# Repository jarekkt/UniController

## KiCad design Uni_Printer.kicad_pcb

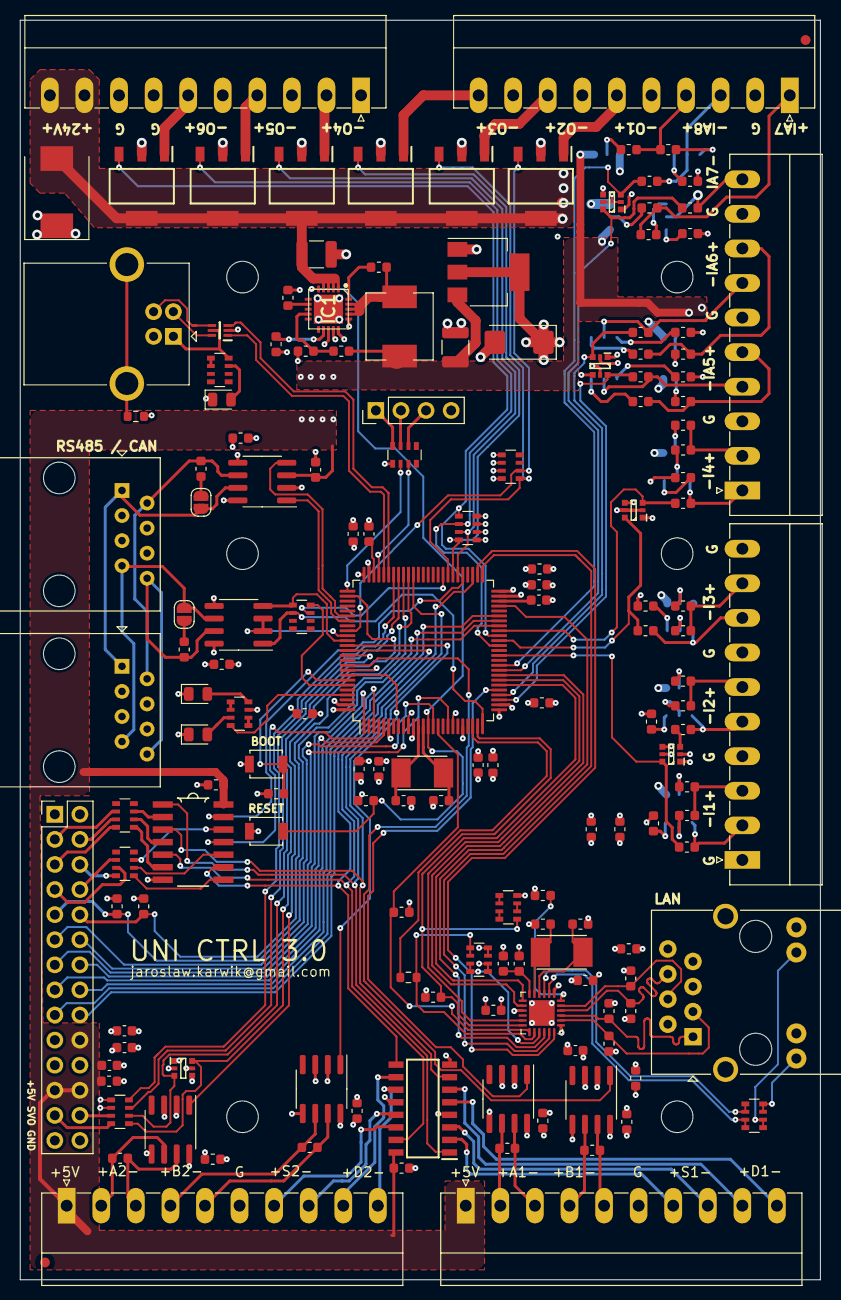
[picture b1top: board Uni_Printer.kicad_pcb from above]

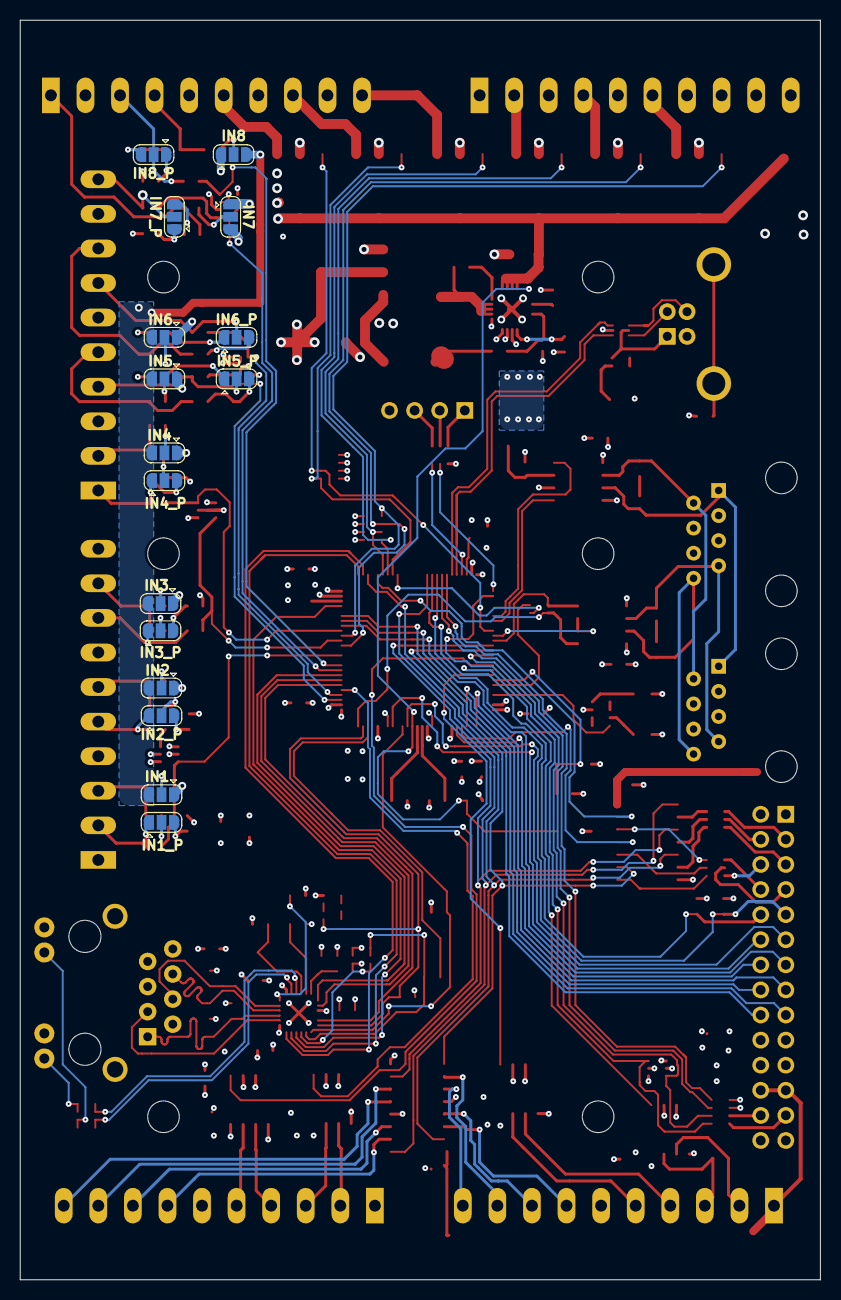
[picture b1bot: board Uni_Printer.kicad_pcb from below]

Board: 4 copper layers, 81.0 x 127.5 mm, 179 parts (16 on the bottom side), 189 nets.

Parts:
C1, C2, C3, C12, C14, C15, C16, C17, C20, C21, C22, C24, C25, C26, C27, C28, C29, C30, C31, C32, C33, C34, C35, C36, C37: 100n; C_0603_1608Metric
C4, C5, C6, C7, C18, C19: 18pF; C_0603_1608Metric
C8, C9, C10, C11, C13, C23, C38: 10uF; C_0603_1608Metric
C39, C41: 2.2uF; C_0603_1608Metric
C40: 10uF 50V; C_1210_3225Metric
C42: 5.6nF; C_0603_1608Metric
C43: 22uF 25V; C_1210_3225Metric
C44: 100uF 6.3V Tantal; CP_EIA-6032-28_Kemet-C
CP2: 470pF; C_0603_1608Metric
D1, D4, D5, D7, D8: D_Schottky_x4_BAV99S; SOT-363
D2, D3, D9: LED; LED_0805_2012Metric
D6: NUF2042XV6T1G; SOT50P160X60-6N
D10: SMCJ24CA; D_SMC
IC1: MAX17503ATP+; QFN50P400X400X80-21N
IC2: AM26C31CD; SOIC127P600X175-16N
IC3: 74HC14D; SO14
IC4: TLV1117-33; SOT-223-3_TabPin2
IC5: LAN8742A; QFN-24-1EP_4x4mm_P0.5mm_EP2.6x2.6mm
IC6, IC7, IC8, IC9, IC10, IC11: ITS4141NHUMA1; SOT230P700X170-4N
J1, J2, J3, J4, J7, J8: Conn_01x10; PhoenixContact_MC-G_10x3.50mm_Angled
J5, J6: FIDUCIAL; Fiducial_1mm_Dia_2mm_Outer
J9, J12: RJ45; RJ45_Amphenol_54602-x08_Horizontal
J10: USB B connector; USB_B_OST_USB-B1HSxx_Horizontal
J11: LMJ1998824110DL1T39J
J13: Conn_01x04_Male; PinHeader_1x04_P2.54mm_Vertical
J14: Conn_02x13_Odd_Even; PinHeader_2x14_P2.54mm_Vertical
JP1: IN1_P; SolderJumper-3-open
JP2: IN2_P; SolderJumper-3-open
JP3: IN3_P; SolderJumper-3-open
JP4: IN4_P; SolderJumper-3-open
JP5, JP6: Jumper; SolderJumper-2_P1.3mm_Open_RoundedPad1.0x1.5mm
JP7: IN1; SolderJumper-3-open
JP8: IN2; SolderJumper-3-open
JP9: IN3; SolderJumper-3-open
JP10: IN4; SolderJumper-3-open
JP11: IN5; SolderJumper-3-open
JP12: IN5_P; SolderJumper-3-open
JP13: IN6; SolderJumper-3-open
JP14: IN6_P; SolderJumper-3-open
JP15: IN7; SolderJumper-3-open
JP16: IN7_P; SolderJumper-3-open
JP17: IN8; SolderJumper-3-open
JP18: IN8_P; SolderJumper-3-open
L1: 10nH; L_0603_1608Metric
L2: 10uH; HPI0630
MK1, MK2, MK3, MK4, MK5, MK6: Mounting_Hole; MountingHole_3.2mm_M3
R1: 33; R_0603_1608Metric
R3, R4, R5: 2k2; R_0603_1608Metric
R6, R10, R14, R18, R27, R31, R35, R42: 1k; R_0603_1608Metric
R7, R9, R11, R13, R15, R17, R19, R21, R26, R29, R30, R33, R34, R37, R41, R44: 10k; R_0603_1608Metric
R8, R12, R16, R20, R22, R23, R24, R25, R28, R32, R36, R39, R40, R43: 120R; R_0603_1608Metric
R38: 12k1; R_0603_1608Metric
R45, R46, R47, R48: 49R9; R_0603_1608Metric
R49: 0R; R_0603_1608Metric
R52: 178k; R_0603_1608Metric
R53: 39k; R_0603_1608Metric
RN1, RN4, RN5, RN6, RN7, RN8, RN9: 100R; R_Array_Convex_4x0603
RN2, RN12, RN13: 10k; R_Array_Convex_4x0603
RN3, RN10: 390R; R_Array_Convex_4x0603
SW2, SW3: SW_Push; SW_SPST_B3U-1000P
U1: STM32H743VIT6; LQFP-100_14x14mm_P0.5mm
U3: TLE9251VSJ; SOIC-8_3.9x4.9mm_P1.27mm
U5, U6, U7, U8, U9: ST1480ACDR; SOIC-8_3.9x4.9mm_P1.27mm
Y1, Y2: ABM7-25.000MHZ-D2Y-T; XTAL500X320X130N_v2

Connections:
+3V3: C3.1, C8.1, C10.1, C12.1, C14.1, C15.1, C17.1, C20.1, C22.1, C23.1, C24.1, C27.1, C28.1, C29.1, C30.1, C32.1, C34.1, C44.1, D1.2 (K), D1.5 (K), D4.2 (K), D4.5 (K), D5.2 (K), D5.5 (K), D7.2 (K), D7.5 (K), D8.2 (K), D8.5 (K), IC4.2 (OUT), J14.19, L1.2, R4.1, R5.1, RN1.7 (R2.2), RN5.1 (R1.1), SW2.1, U1.6 (VBAT), U1.11 (VDD), U1.21 (VDDA), U1.27 (VDD), U1.50 (VDD), U1.75 (VDD), U1.100 (VDD), U3.5 (VIO), U5.8 (VCC), U6.8 (VCC), U7.8 (VCC), U8.8 (VCC), U9.8 (VCC)
+5V: C2.1, C25.1, C26.2, C31.1, C38.1, C43.1, IC2.16 (VCC), IC3.14 (VCC), IC4.3 (IN), J7.1, J8.1, J14.20, J14.23, J14.24, JP7.3 (B), JP8.3 (B), JP9.3 (B), JP10.3 (B), JP11.3 (B), JP13.3 (B), JP15.3 (B), JP17.3 (B), L2.2, R52.1, U3.3 (VCC)
/ADC.CH1: J14.11, U1.15 (PC0)
/ADC.CH2: J14.12, U1.18 (PC3_C)
/AIN_IN_ADC5: D7.6 (C), R27.2, U1.28 (PA4)
/AIN_IN_ADC6: D7.3 (C), R31.2, U1.29 (PA5)
/AIN_IN_ADC7: D8.6 (C), R35.2, U1.34 (PB0)
/AIN_IN_ADC8: D8.3 (C), R42.2, U1.35 (PB1)
/Analod / Digital IO/OUT_E1: J14.3, RN6.6 (R3.2)
/Analod / Digital IO/OUT_E2: J14.4, RN6.7 (R2.2)
/Analod / Digital IO/OUT_E3: J14.5, RN6.8 (R1.2)
/Analod / Digital IO/OUT_E4: J14.6, RN7.8 (R1.2)
/Analod / Digital IO/OUT_E5: J14.7, RN7.7 (R2.2)
/Analod / Digital IO/OUT_E6: J14.8, RN7.6 (R3.2)
/Connectors/AIN_IN5: J4.4, JP12.2 (C), R27.1
/Connectors/AIN_IN6: J4.7, JP14.2 (C), R31.1
/Connectors/AIN_IN7: J4.10, JP16.2 (C), R35.1
/Connectors/AIN_IN8: J3.3, JP18.2 (C), R42.1
/Connectors/AIN_IN_SUP5: J4.5, R28.2, R29.2
/Connectors/AIN_IN_SUP6: J4.8, R32.2, R33.2
/Connectors/AIN_IN_SUP7: J3.1, R36.2, R37.2
/Connectors/AIN_IN_SUP8: J3.4, R43.2, R44.2
/Connectors/DIR1.A: IC2.6 (2Y), J7.9
/Connectors/DIR1.B: IC2.5 (2Z), J7.10
/Connectors/DIR2.A: IC2.10 (3Y), J8.9
/Connectors/DIR2.B: IC2.11 (3Z), J8.10
/Connectors/ENC1_IN.A1: J7.2, R23.1, U5.6 (A)
/Connectors/ENC1_IN.A2: J7.4, R22.1, U6.6 (A)
/Connectors/ENC1_IN.B1: J7.3, R23.2, U5.7 (B)
/Connectors/ENC1_IN.B2: J7.5, R22.2, U6.7 (B)
/Connectors/ENC2_IN.A1: J8.2, R25.1, U7.6 (A)
/Connectors/ENC2_IN.A2: J8.4, R24.1, U8.6 (A)
/Connectors/ENC2_IN.B1: J8.3, R25.2, U7.7 (B)
/Connectors/ENC2_IN.B2: J8.5, R24.2, U8.7 (B)
/Connectors/FDCAN_H: J9.1, J12.1, JP6.2, U3.7 (CANH)
/Connectors/FDCAN_L: J9.2, J12.2, R40.2, U3.6 (CANL)
/Connectors/IN1: J1.2, JP1.1 (A), R6.1
/Connectors/IN2: J1.5, JP2.1 (A), R10.1
/Connectors/IN3: J1.8, JP3.1 (A), R14.1
/Connectors/IN4: J4.1, JP4.1 (A), R18.1
/Connectors/IN_SUP1: J1.3, R8.2, R9.2
/Connectors/IN_SUP2: J1.6, R12.2, R13.2
/Connectors/IN_SUP3: J1.9, R16.2, R17.2
/Connectors/IN_SUP4: J4.2, R20.2, R21.2
/Connectors/OUT_HSW1: IC8.1 (OUT), J3.6
/Connectors/OUT_HSW2: IC7.1 (OUT), J3.8
/Connectors/OUT_HSW3: IC11.1 (OUT), J3.10
/Connectors/OUT_HSW4: IC10.1 (OUT), J2.2
/Connectors/OUT_HSW5: IC9.1 (OUT), J2.4
/Connectors/OUT_HSW6: IC6.1 (OUT), J2.6
/Connectors/RS_485_A: J9.7, J12.7, JP5.2, U9.6 (A)
/Connectors/RS_485_B: J9.8, J12.8, R39.2, U9.7 (B)
/Connectors/STEP1.A: IC2.2 (1Y), J7.7
/Connectors/STEP1.B: IC2.3 (1Z), J7.8
/Connectors/STEP2.A: IC2.14 (4Y), J8.7
/Connectors/STEP2.B: IC2.13 (4Z), J8.8
/Connectors/SUPPY+: C40.1, D10.2 (A2), IC1.1 (VIN_1), IC1.2 (VIN_2), IC1.3 (VIN_3), IC1.4 (EN/UVLO), IC6.4 (VBB), IC7.4 (VBB), IC8.4 (VBB), IC9.4 (VBB), IC10.4 (VBB), IC11.4 (VBB), J2.9, J2.10, JP7.1 (A), JP8.1 (A), JP9.1 (A), JP10.1 (A), JP11.1 (A), JP13.1 (A), JP15.1 (A), JP17.1 (A)
/Digital Inputs/IN_CPU: D4.3 (C), R10.2
/ENC1.CH1: U1.30 (PA6), U5.1 (RO)
/ENC1.CH2: U1.91 (PB5), U6.1 (RO)
/ENC2.CH1: U1.92 (PB6), U7.1 (RO)
/ENC2.CH2: U1.93 (PB7), U8.1 (RO)
/Ethernet/ENET_CRSDV: IC5.11 (CRS_DV/MODE2), U1.31 (PA7)
/Ethernet/ENET_MDC: C7.1, IC5.13 (MDC), U1.16 (PC1)
/Ethernet/ENET_MDIO: C6.1, IC5.12 (MDIO), RN3.1 (R1.1), U1.24 (PA2)
/Ethernet/ENET_REF_CLK: R1.1, U1.23 (PA1)
/Ethernet/ENET_RST: IC5.15 (RST), RN2.7 (R2.2), RN2.8 (R1.2)
/Ethernet/ENET_RXD0: IC5.8 (RXD0/MODE0), U1.32 (PC4)
/Ethernet/ENET_RXD1: IC5.7 (RXD1/MODE1), U1.33 (PC5)
/Ethernet/ENET_TXD0: IC5.17 (TXD0), U1.51 (PB12)
/Ethernet/ENET_TXD1: IC5.18 (TXD1), U1.52 (PB13)
/Ethernet/ENET_TX_EN: IC5.16 (TXEN), U1.47 (PB11)
/Ethernet/RJ45_LED1: J11.9 (LEDG_A), RN10.7 (R2.2), RN10.8 (R1.2)
/Ethernet/RJ45_LED2: J11.11 (LEDY_A), RN10.5 (R4.2), RN10.6 (R3.2)
/Ethernet/RX+: IC5.23 (RXP), J11.4 (RD+), R47.1
/Ethernet/RX-: IC5.22 (RXN), J11.6 (RD-), R48.1
/Ethernet/TX+: IC5.21 (TXP), J11.1 (TD+), R45.1
/Ethernet/TX-: IC5.20 (TXN), J11.3 (TD-), R46.1
/Ethernet/VDD: C9.1, C21.2, C33.2, C35.2, C36.1, C37.1, IC5.1 (VDD2A), IC5.9 (VDDIO), IC5.19 (VDD1A), J11.2 (TCT), J11.5 (RCT), L1.1, R45.2, R46.2, R47.2, R48.2, RN2.1 (R1.1), RN2.2 (R2.1), RN2.3 (R3.1), RN2.4 (R4.1), RN3.4 (R4.1)
/Ethernet/VDDCR: C39.1, CP2.1, IC5.6 (VDDCR)
/FDCAN_RX: U1.81 (PD0), U3.4 (RXD)
/FDCAN_TX: U1.82 (PD1), U3.1 (TXD)
/I2C.SCL: J14.9, R5.2, U1.67 (PA8)
/I2C.SDA: J14.10, R4.2, U1.66 (PC9)
/IN_CPU1: D4.6 (C), R6.2, U1.37 (PE7)
/IN_CPU3: D5.6 (C), R14.2, U1.40 (PE10)
/IN_CPU4: D5.3 (C), R18.2, U1.42 (PE12)
/MID_IO1: J14.17, U1.44 (PE14)
/MID_IO2: J14.18, U1.45 (PE15)
/OUT_CPU1: IC8.3 (IN), RN12.2 (R2.1), U1.84 (PD3)
/OUT_CPU2: IC7.3 (IN), RN12.1 (R1.1), U1.58 (PD11)
/OUT_CPU3: IC11.3 (IN), RN13.4 (R4.1), U1.57 (PD10)
/OUT_CPU4: IC10.3 (IN), RN13.3 (R3.1), U1.56 (PD9)
/OUT_CPU5: IC9.3 (IN), RN13.2 (R2.1), U1.39 (PE9)
/OUT_CPU6: IC6.3 (IN), RN13.1 (R1.1), U1.41 (PE11)
/OUT_DIR1: IC2.7 (2A), IC3.3 (I), U1.87 (PD6)
/OUT_DIR2: IC2.9 (3A), IC3.9 (I), U1.88 (PD7)
/OUT_DIR3: IC3.13 (I), U1.55 (PD8)
/OUT_STEP1: IC2.1 (1A), IC3.1 (I), U1.65 (PC8)
/OUT_STEP2: IC2.15 (4A), IC3.5 (I), U1.53 (PB14)
/OUT_STEP3: IC3.11 (I), U1.4 (PE5)
/Power_supply/PWR_RESET: C16.1, IC1.5 (~RESET), SW3.2, U1.14 (NRST)
/Processor/BOOT0: R3.1, SW2.2, U1.94 (BOOT0)
/Processor/D+: D6.3 (D2_1), U1.70 (PA11)
/Processor/D-: D6.1 (D1_1), U1.71 (PA12)
/Processor/LED: RN1.4 (R4.1), U1.97 (PE0)
/Processor/LPTM1_IN1_PD12: RN4.3 (R3.1), U1.59 (PD12)
/Processor/SWCLK: RN5.2 (R2.1), U1.76 (PA14)
/Processor/SWDIO: RN5.3 (R3.1), U1.72 (PA13)
/Processor/TIM16_CH1__PB8: RN4.4 (R4.1), U1.95 (PB8)
/RS485_DE: U1.85 (PD4), U9.2 (~RE), U9.3 (DE)
/RS485_RX: RN4.5 (R4.2), U1.86 (PD5), U9.4 (DI)
/RS485_TX: RN4.6 (R3.2), U1.25 (PA3), U9.1 (RO)
/SPI.MISO: J14.13, U1.43 (PE13)
/SPI.MOSI: J14.14, U1.5 (PE6)
/SPI.NSS: J14.16, U1.3 (PE4)
/SPI.SCLK: J14.15, U1.1 (PE2)
/TIM.CH1: D1.6 (C), RN9.1 (R1.1), U1.77 (PA15)
/TIM.CH2: D1.3 (C), RN9.2 (R2.1), U1.89 (PB3)
/UART.RX: RN9.4 (R4.1), U1.69 (PA10)
/UART.TX: RN9.3 (R3.1), U1.68 (PA9)
/USB.D+: D6.6 (D1_2), J10.2 (D-)
/USB.D-: D6.4 (D2_2), J10.3 (D+)
/USB.VBUS: D6.5 (VBUS), J10.1 (VBUS), RN8.4 (R4.1)
/midboard/RES_TIM.CH1: J14.25, RN9.8 (R1.2)
/midboard/RES_TIM.CH2: J14.26, RN9.7 (R2.2)
/midboard/RES_UART.RX: J14.2, RN9.5 (R4.2)
/midboard/RES_UART.TX: J14.1, RN9.6 (R3.2)
GND: C2.2, C3.2, C4.2, C5.2, C6.2, C7.2, C8.2, C9.2, C10.2, C11.2, C12.2, C13.2, C14.2, C15.2, C16.2, C17.2, C18.2, C19.2, C20.2, C21.1, C22.2, C23.2, C24.2, C25.2, C26.1, C27.2, C28.2, C29.2, C30.2, C31.2, C32.2, C33.1, C34.2, C35.1, C36.2, C37.2, C38.2, C39.2, C40.2, C41.2, C42.1, C43.2, C44.2, CP2.2, D1.1 (A), D1.4 (A), D2.1 (K), D3.1 (K), D4.1 (A), D4.4 (A), D5.1 (A), D5.4 (A), D6.2 (GND), D7.1 (A), D7.4 (A), D8.1 (A), D8.4 (A), D9.1 (K), D10.1 (A1), IC1.13 (SGND), IC1.14 (PGND_1), IC1.15 (PGND_2), IC1.16 (PGND_3), IC1.21 (EP), IC2.4 (G), IC2.8 (GND), IC2.12 (~G), IC3.7 (GND), IC4.1 (GND), IC5.25 (VSS), IC6.2 (GND), IC7.2 (GND), IC8.2 (GND), IC9.2 (GND), IC10.2 (GND), IC11.2 (GND), J1.1, J1.4, J1.7, J1.10, J2.1, J2.3, J2.5, J2.7, J2.8, J3.2, J3.5, J3.7, J3.9, J4.3, J4.6, J4.9, J7.6, J8.6, J9.3, J9.4, J9.5, J9.6, J10.4 (GND), J11.8, J11.10 (LEDG_K), J11.12 (LEDY_K), J11.SH (SHIELD), J12.3, J12.4, J12.5, J12.6, J13.4, J14.21, J14.22, J14.27, J14.28, R3.2, R7.1, R11.1, R15.1, R19.1, R26.1, R30.1, R34.1, R38.2, R41.1, R49.2, R53.2, RN12.5 (R4.2), RN12.6 (R3.2), RN12.7 (R2.2), RN12.8 (R1.2), RN13.5 (R4.2), RN13.6 (R3.2), RN13.7 (R2.2), RN13.8 (R1.2), SW3.1, U1.10 (VSS), U1.19 (VSSA), U1.26 (VSS), U1.49 (VSS), U1.74 (VSS), U1.99 (VSS), U3.2 (GND), U3.8 (STB), U5.2 (~RE), U5.3 (DE), U5.5 (GND), U6.2 (~RE), U6.3 (DE), U6.5 (GND), U7.2 (~RE), U7.3 (DE), U7.5 (GND), U8.2 (~RE), U8.3 (DE), U8.5 (GND), U9.5 (GND)
unnamed: C1.1, IC1.20 (BST)
unnamed: C1.2, IC1.17 (LX_1), IC1.18 (LX_2), IC1.19 (LX_3), L2.1
unnamed: C4.1, IC5.5 (XTAL1/CLKIN), Y2.1
unnamed: C5.1, IC5.4 (XTAL2), Y2.2
unnamed: C11.1, U1.48 (VCAP1)
unnamed: C13.1, U1.73 (VCAP2)
unnamed: C18.1, U1.12 (PH0), Y1.1
unnamed: C19.1, U1.13 (PH1), Y1.2
unnamed: C41.1, IC1.12 (VCC)
unnamed: C42.2, IC1.7 (SS)
unnamed: D2.2 (A), RN1.8 (R1.2)
unnamed: D3.2 (A), RN1.3 (R3.1)
unnamed: D9.2 (A), RN8.3 (R3.1)
unnamed: IC1.9 (FB), R52.2, R53.1
unnamed: IC3.2 (O), RN6.3 (R3.1)
unnamed: IC3.4 (O), RN6.2 (R2.1)
unnamed: IC3.6 (O), RN6.1 (R1.1)
unnamed: IC3.8 (O), RN7.1 (R1.1)
unnamed: IC3.10 (O), RN7.2 (R2.1)
unnamed: IC3.12 (O), RN7.3 (R3.1)
unnamed: IC5.2 (LED2/nINTSEL), RN10.3 (R3.1), RN10.4 (R4.1)
unnamed: IC5.3 (LED1/REGOFF), RN10.1 (R1.1), RN10.2 (R2.1)
unnamed: IC5.14 (INT/REFCLKO), R1.2, RN2.5 (R4.2), RN2.6 (R3.2)
unnamed: IC5.24 (RBIAS), R38.1
unnamed: J10.5 (Shield), R49.1
unnamed: J13.1, RN5.8 (R1.2)
unnamed: J13.2, RN5.7 (R2.2)
unnamed: J13.3, RN5.6 (R3.2)
unnamed: JP1.2 (C), R9.1
unnamed: JP1.3 (B), R7.2
unnamed: JP2.2 (C), R13.1
unnamed: JP2.3 (B), R11.2
unnamed: JP3.2 (C), R17.1
unnamed: JP3.3 (B), R15.2
unnamed: JP4.2 (C), R21.1
unnamed: JP4.3 (B), R19.2
unnamed: JP5.1, R39.1
unnamed: JP6.1, R40.1
unnamed: JP7.2 (C), R8.1
unnamed: JP8.2 (C), R12.1
unnamed: JP9.2 (C), R16.1
unnamed: JP10.2 (C), R20.1
unnamed: JP11.2 (C), R28.1
unnamed: JP12.1 (A), R26.2
unnamed: JP12.3 (B), R29.1
unnamed: JP13.2 (C), R32.1
unnamed: JP14.1 (A), R30.2
unnamed: JP14.3 (B), R33.1
unnamed: JP15.2 (C), R36.1
unnamed: JP16.1 (A), R34.2
unnamed: JP16.3 (B), R37.1
unnamed: JP17.2 (C), R43.1
unnamed: JP18.1 (A), R41.2
unnamed: JP18.3 (B), R44.1
unnamed: RN1.1 (R1.1), RN1.2 (R2.1)
unnamed: RN1.5 (R4.2), RN1.6 (R3.2)
unnamed: RN3.2 (R2.1), RN3.3 (R3.1)
unnamed: RN3.5 (R4.2), RN3.6 (R3.2)
unnamed: RN3.7 (R2.2), RN3.8 (R1.2)
unnamed: RN8.5 (R4.2), RN8.6 (R3.2)

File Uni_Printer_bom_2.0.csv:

Component,Description,Part,References,Value,Footprint,Quantity Per PCB,Datasheet,TME,Category,Mouser Price/Stock,Mouser Part Number,Manufacturer_Name,Height,RS Price/Stock,RS Part Number,Manufacturer_Part_Number,Arrow Part Number,Arrow Price/Stock,TME-WTYK,TME-GNIAZDO,Digi,MFG num
1,,C-Device,C4 C5 C18 C19,18pF,C_0603_1608Metric,4,~,VJ0603A180JXACW2BC,,,,,,,,,,,,,,
2,Unpolarized capacitor,C,C6 C7,18p,C_0603_1608Metric,2,~,,,,,,,,,,,,,,,
3,"Unpolarized capacitor, small symbol",C_Small,C42,5.6nF,C_0603_1608Metric,1,~,,,,,,,,,,,,,,,
4,"Unpolarized capacitor, small symbol",C_Small,C1 C21 C33 C35 C36 C37,100nF,C_0603_1608Metric,6,~,,,,,,,,,,,,,,,
5,,C-Device,C12 C14 C15 C16 C17 C20 C22 C24 C26 C31,100n,C_0603_1608Metric,10,~,C0603C104K3RAC,,,,,,,,,,,,,,
6,,C,C2 C3,100n,C_0603_1608Metric,2,,,Capacitor,,,,,,,,,,,,,
7,,C_Small-Device,C25 C27 C28 C29 C30 C34,100n,C_0603_1608Metric,6,~,C0603C104K3RAC WF06P-120R-5%,,,,,,,,,,,,,,
8,,C_Small-Sensor_tank_v1-rescue-Uni_General_v1-rescue-Uni_Printer_v1-rescue,C32,100n,C_0603_1608Metric,1,,C0603C104K3RAC,,,,,,,,,,,,,,
9,"Unpolarized capacitor, small symbol",C_Small,C41,2.2uF,C_0603_1608Metric,1,~,,,,,,,,,,,,,,,
10,,C-Device,C8 C10 C11 C13 C23 C38,10uF,C_1206_3216Metric,6,~,0805X106K100CT,,,,,,,,,,,,,,
11,"Unpolarized capacitor, small symbol",C_Small,C9,10uF,C_0603_1608Metric,1,~,,,,,,,,,,,,,,,
12,"Unpolarized capacitor, small symbol",C_Small,C44,100uF 6.3V Tantal,CP_EIA-6032-28_Kemet-C,1,~,,,,,,,,,,,,,,,
13,"Unpolarized capacitor, small symbol",C_Small,C40,10uF 50V,C_1210_3225Metric,1,~,,,,,,,,,,,,,,,
14,"Unpolarized capacitor, small symbol",C_Small,C43,22uF 25V,C_1206_3216Metric,1,~,,,,,,,,,,,,,,,
15,"Polarized capacitor, US symbol",CP1,CP1,1.0uF/1.0ESR,C_0603_1608Metric,1,~,,,,,,,,,,,,,,,
16,"Polarized capacitor, US symbol",CP1,CP2,470pF,C_0603_1608Metric,1,~,,,,,,,,,,,,,,,
17,,D_Schottky_x4_BAV99S-RESCUE-step2cnc-Sensor_tank_v1-rescue-Uni_General_v1-rescue-Uni_Printer_v1-rescue,D1 D4 D5 D7 D8,D_Schottky_x4_BAV99S,SOT-363,5,,BAV99S.115,,,,,,,,,,,,,,
18,,LED-Sensor_tank_v1-rescue-Uni_General_v1-rescue-Uni_Printer_v1-rescue,D2 D3 D9,LED,LED_0805_2012Metric,3,,,,,,,,,,,,,,,,
19,,NUF2042XV6T1G,D6,NUF2042XV6T1G,SOT50P160X60-6N,1,~,,,,,,,,,,,,,,,
20,Bidirectional transient-voltage-suppression diode,D_TVS,D10,SMCJ24CA,D_SMC,1,~,SMCJ24CA,,,,,,,,,,,,,,
21,,74*14-step2cnc-Uni_Printer_v1-rescue,IC3,74HC14D,SO14,1,~,,,,,,,,,,,,,,,
22,,AM26C31CD-AM26C31CD-Uni_Printer_v1-rescue,IC2,AM26C31CD,SOIC127P600X175-16N,1,http://www.ti.com/lit/ds/symlink/am26c31.pdf,,,https://www.mouser.com/Search/Refine.aspx?Keyword=595-AM26C31CD,595-AM26C31CD,Texas Instruments,1.75,http://uk.rs-online.com/web/p/products/5170520P,5170520P,AM26C31CD,,,,,,
23,,ITS4141NHUMA1,IC6 IC7 IC8 IC9 IC10 IC11,ITS4141NHUMA1,SOT230P700X170-4N,6,http://www.farnell.com/datasheets/8560http://www.infineon.co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,,,https://www.mouser.co.uk/ProductDetail/Infineon-Technologies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,726-ITS4141NHUMA1,Infineon,1.7,,,ITS4141NHUMA1,ITS4141NHUMA1,https://www.arrow.com/en/products/its4141nhuma1/infineon-tec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,,,,
24,,LAN8720A,IC5,LAN8742A,QFN-24-1EP_4x4mm_P0.5mm_EP2.6x2.6mm,1,,,,,,,,,,,,,,,,
25,,MAX17503ATP+,IC1,MAX17503ATP+,QFN50P400X400X80-21N,1,https://pdfserv.maximintegrated.com/en/ds/MAX17503.pdf,,,https://www.mouser.com/Search/Refine.aspx?Keyword=700-MAX175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,700-MAX17503ATP+,Maxim Integrated,0.8,,,MAX17503ATP+,,,,,,
26,,LM1117-step2cnc-Sensor_tank_v1-rescue-Uni_General_v1-rescue-Uni_Printer_v1-rescue-Uni_Printer-rescue,IC4,TLV1117-33,SOT-223-3_TabPin2,1,,TLV1117-33CDCYG3,,,,,,,,,,,,,,
27,"Generic connector, single row, 01x04, script generated (kicad-library-utils/schlib/autogen/connector/)",Conn_01x04_Male,J13,Conn_01x04_Male,PinHeader_1x04_P2.54mm_Vertical,1,~,,,,,,,,,,,,,,,
28,,Conn_01x10-Connector_Generic,J1 J2 J3 J4 J7 J8,Conn_01x10,PhoenixContact_MC-G_10x3.50mm_Angled,6,~,,,,,,,,,,,,15EDGK-3.5/10P,15EDGRC-3.5/10P,,
29,"Generic connector, double row, 02x14, odd/even pin numbering scheme (row 1 odd numbers, row 2 even numbers), script generated (kicad-library-utils/schlib/autogen/connector/)",Conn_02x14_Odd_Even,J14,Conn_02x13_Odd_Even,PinHeader_2x14_P2.54mm_Vertical,1,~,,,,,,,,,,,,,,,
30,,RJ45-TRANSFO_v2-rj12,J11,LMJ1998824110DL1T39J,LMJ1998824110DL1T39J,1,,RJ45-TRAFO-L,,,,,,,,,,,,,,
31,"RJ connector, 8P8C (8 positions 8 connected)",RJ45,J9 J12,RJ45,RJ45_Amphenol_54602-x08_Horizontal,2,~,,,,,,,,,,,,,,,
32,,USB_B-Connector,J10,USB B connector,USB_B_OST_USB-B1HSxx_Horizontal,1,~,TUEB4F2D0B,,,,,,,,,,,,,,
33,,Jumper_3_Bridged12-Jumper,JP1 JP2 JP3 JP4 JP7 JP8 JP9 JP10 JP11 JP12 JP13 JP14 JP15 JP16 JP17 JP18,Jumper,SolderJumper-3_P1.3mm_Bridged2Bar12_RoundedPad1.0x1.5mm,16,~,WF06P-120R-5%,,,,,,,,,,,,,,
34,,Jumper_NO_Small-Device,JP5 JP6,Jumper,SolderJumper-2_P1.3mm_Open_RoundedPad1.0x1.5mm,2,~,,,,,,,,,,,,,,,
35,,INDUCTOR_SMALL,L1,10uH,L_0603_1608Metric,1,,,,,,,,,,,,,,,,
36,"Inductor, small symbol",L_Small,L2,10uH,HPI0630,1,~,HPI0630-100,,,,,,,,,,,,,,
37,,R-Sensor_tank_v1-rescue-Uni_General_v1-rescue-Uni_Printer_v1-rescue,R49,0R,R_0603_1608Metric,1,~,WF06P-120R-5%,,,,,,,,,,,,,,
38,,R-RESCUE-step2cnc8_,R1,33,R_0603_1608Metric,1,~,,,,,,,,,,,,,,,
39,,R-RESCUE-step2cnc8_,R45 R46 R47 R48,49R9,R_0603_1608Metric,4,~,,,,,,,,,,,,,,,
40,,R-Sensor_tank_v1-rescue-Uni_General_v1-rescue-Uni_Printer_v1-rescue,R8 R12 R16 R20 R28 R32 R36 R39 R40 R43,120R,R_0603_1608Metric,10,,CRCW06030000Z0TABC WF06P-120R-5%,,,,,,,,,,,,,,
41,,R-Device,R22 R23 R24 R25,120R,R_0603_1608Metric,4,~,WF06P-120R-5%,,,,,,,,,,,,,,
42,,R-Sensor_tank_v1-rescue-Uni_General_v1-rescue-Uni_Printer_v1-rescue,R6 R10 R14 R18 R27 R31 R35 R42,1k,R_0603_1608Metric,8,,HP03-1K5% WF06P-120R-5%,,,,,,,,,,,,,,
43,,R-Device,R3 R4 R5,2k2,R_0603_1608Metric,3,~,HP03-2K25%,,,,,,,,,,,,,,
44,,R-Sensor_tank_v1-rescue-Uni_General_v1-rescue-Uni_Printer_v1-rescue,R7 R9 R11 R13 R15 R17 R19 R21 R26 R29 R30 R33 R34 R37 R41 R44,10k,R_0603_1608Metric,16,,SMD0603-680R-1% WF06P-120R-5%,,,,,,,,,,,,,,
45,,R-RESCUE-step2cnc8_,R38,12k1,R_0603_1608Metric,1,~,,,,,,,,,,,,,,,
46,"Resistor, small symbol",R_Small,R53,39k,R_0603_1608Metric,1,~,,,,,,,,,,,,,,,
47,"Resistor, small symbol",R_Small,R52,178k,R_0603_1608Metric,1,~,,,,,,,,,,,,,,,
48,,R_Pack04-Device,RN1 RN4 RN5 RN6 RN7 RN8 RN9,100R,R_Array_Convex_4x0603,7,~,DR1206-390K-4/8,,,,,,,,,,,,,,
49,"4 resistor network, parallel topology",R_Pack04,RN2,10k,R_Array_Convex_4x0603,1,~,,,,,,,,,,,,,,,
50,,R_Pack04-Device,RN12 RN13,15k,R_Array_Convex_4x0603,2,~,,,,,,,,,,,,,,,
51,"4 resistor network, parallel topology",R_Pack04,RN3 RN10,390R,R_Array_Convex_4x0603,2,~,,,,,,,,,,,,,,,
52,,SW_Push-Switch,SW2 SW3,SW_Push,SW_SPST_B3U-1000P,2,,B3U-1000PM,,,,,,,,,,,,,,
53,,ST1480ACDR-Sensor_tank_v1-rescue-Uni_General_v1-rescue-Uni_Printer_v1-rescue,U5 U6 U7 U8 U9,ST1480ACDR,SOIC-8_3.9x4.9mm_P1.27mm,5,,SP3077EEN-L SP3485EN-L,,,,,,,,,,,,,,
54,,STM32H743VITx,U1,STM32H743VITx,LQFP-100_14x14mm_P0.5mm,1,,,,,,,,,,,,,,,,
55,,TLE9251VSJ,U3,TLE9251VSJ,SOIC-8_3.9x4.9mm_P1.27mm,1,,,Driver,,,,,,,,,,,,TLE9251VSJXUMA1TR-ND,TLE9251VSJ
56,,Crystal-Device,Y2,ABM7-25.000MHZ-D2Y-T,XTAL500X320X130N_v2,1,~,ABM7-25.000MHZ-D2Y,,,,,,,,,,,,,,
57,,Crystal-Device,Y1,ABM7-8.000MHZ-D2Y-T,XTAL500X320X130N_v2,1,~,ABM7-8.000MHZ-D2Y,,,,,,,,,,,,,,





Component Groups:,57
Component Count:,171
Fitted Components:,171
Number of PCBs:,1
Total components:,171
Schematic Version:,2.0
Schematic Date:,2020-04-30
PCB Variant:,default
BoM Date:,14.01.2021 11:15:03
Schematic Source:,Uni_Printer.kicad_sch
KiCad Version:,Eeschema (5.99.0-7794-gffe7d2ea49)

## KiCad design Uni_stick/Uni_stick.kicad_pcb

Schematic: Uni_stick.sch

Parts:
C1, C4, C5, C8, C9, C10, C13, C14, C26, C28: 100n; C_0603_1608Metric
C2, C3, C6, C7, C11, C12, C15: 47uF; CP_EIA-7343-43_Kemet-X
C25: 100n; C_1206_3216Metric
IC1, IC2: MPX5050DP; Pressure_sensor_v2
IC3: MAX20050ATC_V+; SON50P300X300X80-13N; Manufacturer_Part_Number MAX20050ATC/V+; Mouser Part Number 700-MAX20050ATC/V+
J1, J2, J5, J7: Conn_01x04; PhoenixContact_MCV_1,5_4-G-3.5_1x04_P3.50mm_Vertical
J3, J6, J8: Conn_01x06; PinHeader_1x06_P2.54mm_Vertical
J4: Micro match 6x2; CONN-TE-MICROMATCH-6X2-SMD_CORRECTED
JP1, JP2, JP3, JP4, JP5, JP6, JP7, JP8, JP9: SolderJumper_3_Bridged12; SolderJumper-3_P1.3mm_Bridged12_RoundedPad1.0x1.5mm
L2: L_Small; L_1206_3216Metric
MK1, MK2, MK3, MK4, MK5, MK6: Mounting_Hole; MountingHole_3.2mm_M3
R1, R3, R5: 2k2; R_0603_1608Metric
R2, R4, R6: 0R; R_0603_1608Metric
R7, R9: 10k; R_0603_1608Metric
R8, R10: 15K; R_0603_1608Metric
R13: 0,133R; R_1206_3216Metric
R16: R_Small; R_0603_1608Metric
RV1: R_POT; 3314J-1
SS1, SS2, SS3: STEPSTICK_TRINAMIC2209; STEPSTICK

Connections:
+3V3: C1.1, C5.1, C10.1, J4.7, JP1.2 (C), JP2.2 (C), JP3.2 (C), JP4.2 (C), JP5.2 (C), JP6.2 (C), JP7.2 (C), JP8.2 (C), JP9.2 (C), RV1.1, SS1.2 (VIO), SS2.2 (VIO), SS3.2 (VIO)
+5V: C8.1, C13.1, IC1.3, IC2.3, J4.9
+24V: C2.1, C3.1, C4.1, C6.1, C7.1, C9.1, C11.1, C12.1, C14.1, C15.1, C28.1, J1.1, J1.3, SS1.8 (VM), SS2.8 (VM), SS3.8 (VM)
/ADC_EXT_SEN1: J4.10, R7.1, R8.1
/ADC_EXT_SEN2: J4.12, R9.1, R10.1
/LED1+: IC3.4, R13.1, R16.1
/LIGHT_ON: IC3.5, J4.8
/OUT_EXT1: J4.1, SS1.10 (STEP)
/OUT_EXT2: J4.2, SS1.9 (DIR)
/OUT_EXT3: J4.3, SS2.10 (STEP)
/OUT_EXT4: J4.4, SS2.9 (DIR)
/OUT_EXT5: J4.5, SS3.10 (STEP)
/OUT_EXT6: J4.6, SS3.9 (DIR)
GND: C1.2, C2.2, C3.2, C4.2, C5.2, C6.2, C7.2, C8.2, C9.2, C10.2, C11.2, C12.2, C13.2, C14.2, C15.2, C26.1, C28.2, IC1.2, IC2.2, IC3.1, IC3.7, IC3.13, J1.2, J1.4, J3.1, J4.11, J6.1, J8.1, JP1.3 (B), JP2.3 (B), JP3.3 (B), JP4.3 (B), JP5.3 (B), JP6.3 (B), JP7.3 (B), JP8.3 (B), JP9.3 (B), R8.2, R10.2, R16.2, RV1.3, SS1.1 (GND), SS1.7 (GND), SS1.16 (~ENABLE), SS2.1 (GND), SS2.7 (GND), SS2.16 (~ENABLE), SS3.1 (GND), SS3.7 (GND), SS3.16 (~ENABLE)
unnamed: C25.1, IC3.11, IC3.12, L2.1
unnamed: C25.2, IC3.10
unnamed: C26.2, IC3.9
unnamed: IC1.1, R7.2
unnamed: IC2.1, R9.2
unnamed: IC3.3, L2.2, R13.2
unnamed: IC3.8, RV1.2
unnamed: J2.1, SS1.6 (M2B)
unnamed: J2.2, SS1.5 (M2A)
unnamed: J2.3, SS1.4 (M1A)
unnamed: J2.4, SS1.3 (M1B)
unnamed: J3.4, R1.1
unnamed: J3.5, R1.2, R2.2, SS1.11 (PDNU1)
unnamed: J5.1, SS2.6 (M2B)
unnamed: J5.2, SS2.5 (M2A)
unnamed: J5.3, SS2.4 (M1A)
unnamed: J5.4, SS2.3 (M1B)
unnamed: J6.4, R3.1
unnamed: J6.5, R3.2, R4.2, SS2.11 (PDNU1)
unnamed: J7.1, SS3.6 (M2B)
unnamed: J7.2, SS3.5 (M2A)
unnamed: J7.3, SS3.4 (M1A)
unnamed: J7.4, SS3.3 (M1B)
unnamed: J8.4, R5.1
unnamed: J8.5, R5.2, R6.2, SS3.11 (PDNU1)
unnamed: JP1.1 (A), SS1.13 (SPREAD)
unnamed: JP2.1 (A), SS1.14 (MS2)
unnamed: JP3.1 (A), SS1.15 (MS1)
unnamed: JP4.1 (A), SS2.13 (SPREAD)
unnamed: JP5.1 (A), SS2.14 (MS2)
unnamed: JP6.1 (A), SS2.15 (MS1)
unnamed: JP7.1 (A), SS3.13 (SPREAD)
unnamed: JP8.1 (A), SS3.14 (MS2)
unnamed: JP9.1 (A), SS3.15 (MS1)
unnamed: R2.1, SS1.12 (PDNU2)
unnamed: R4.1, SS2.12 (PDNU2)
unnamed: R6.1, SS3.12 (PDNU2)

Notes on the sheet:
Spread cycle by default
FTDI connector
1/16 by default

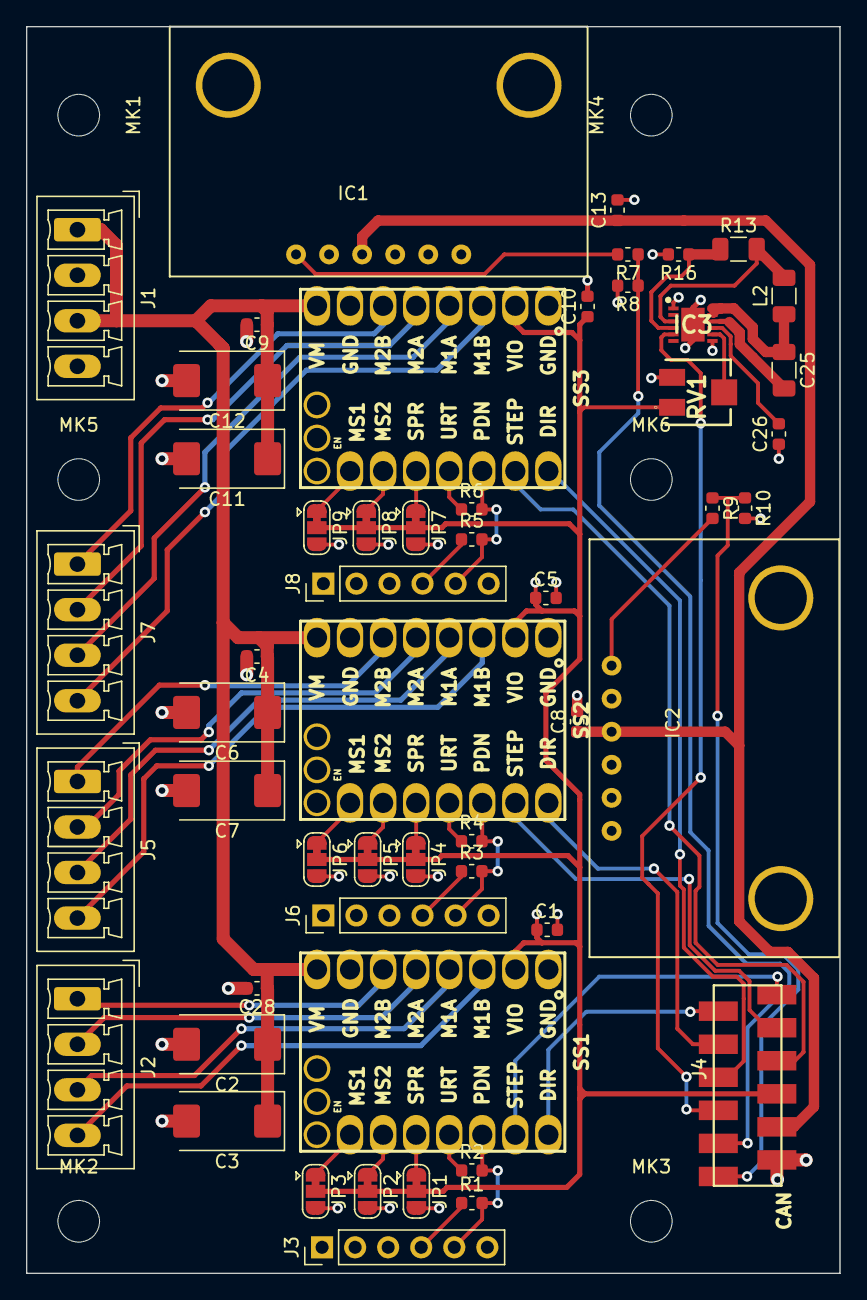
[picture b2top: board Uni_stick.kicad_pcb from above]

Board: 2 copper layers, 62.5 x 95.8 mm, 59 parts (0 on the bottom side), 51 nets.
